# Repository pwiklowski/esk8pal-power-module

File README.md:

# esk8pal power module

This repository contains eagle project for power board that is used in esp8pal project. It contains DC-DC converter, current and voltage sensor connected do ADC chip. Board used i2c interface to connect with main board. 

 For other repositories from esk8pal project go to:

- Frontend Angular Appplication - https://github.com/pwiklowski/esk8pal-web-be
- Backend service - https://github.com/pwiklowski/esk8pal-web-be
- ESP32 Firmware - https://github.com/pwiklowski/esk8pal-device
- PWA companion application that uses Web Bluetooth API (WIP)- https://github.com/pwiklowski/esk8pal-pwa
- Android application - https://github.com/pwiklowski/esk8pal-android

## Schematic

## PCB

## Prototype

## New PCB's - power module 0.2.0 and main board 0.1.

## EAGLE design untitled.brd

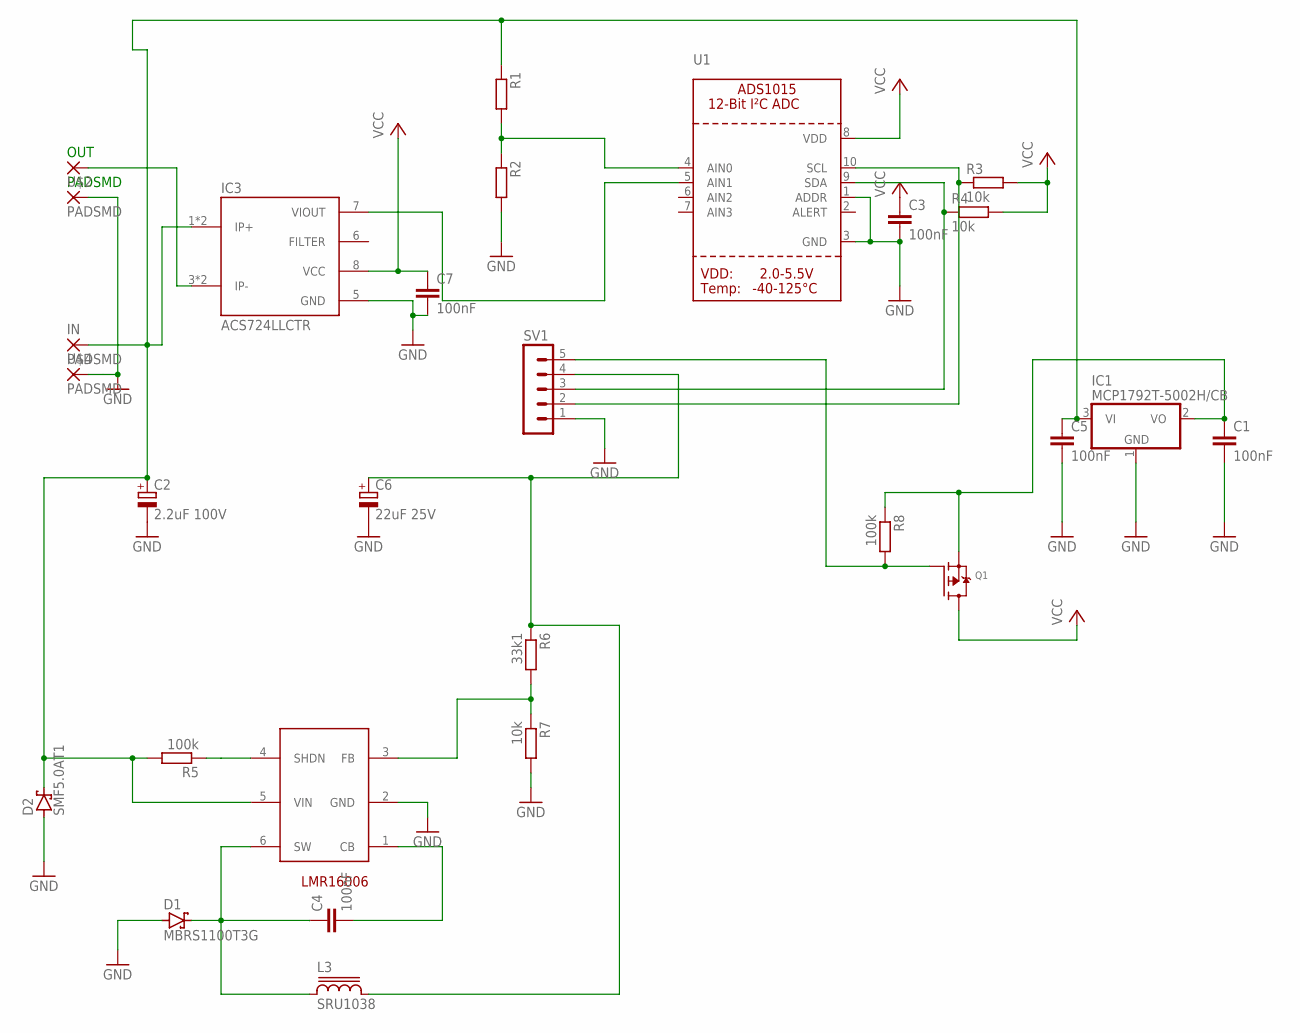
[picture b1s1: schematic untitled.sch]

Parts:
C1, C3, C4, C5, C7: 100nF; C0805
C2: 2.2uF 100V; B/3528-21R
C6: 22uF 25V; R/2012-12R
D1: MBRS1100T3G; SOD323_ST
D2: SMF5.0AT1; SOD123FL
IC1: MCP1792T-5002H/CB; SOT23
IC3: ACS724LLCTR; SO08
IN: PADSMD; PADS
L3: SRU1038
OUT: PADSMD; PADS
Q1: MOSFET-PWIDE; SOT23-WIDE
R1, R2: R-EU_R0805; R0805
R3, R4: 10k; R0805
R5: 100k; M0805
R6: 33k1; M0805
R7: 10k; M0805
R8: 100k; R0805
SV1: MA05-1
U1: ADC_ADS1015; MSOP10
U$2, U$4: PADSMD; PADS
U$5: LMR16006; TSOT23-6_DDC

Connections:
GND: C1.2, C2.-, C3.2, C5.2, C6.-, C7.2, D1.A, D2.A, IC1.1 (GND), IC3.5 (GND), R2.2, R7.2, SV1.1, U1.1 (ADDR), U1.3 (GND), U$2.P$1, U$4.P$1, U$5.2 (GND)
unnamed: IC3.7 (VIOUT), U1.5 (AIN1)
unnamed: IC3.3 (IP-), IC3.4 (IP-), OUT.P$1
unnamed: R5.1, U$5.4 (SHDN)
unnamed: C2.+, C5.1, D2.C, IC1.3 (VI), IC3.1 (IP+), IC3.2 (IP+), IN.P$1, R1.1, R5.2, U$5.5 (VIN)
unnamed: R4.1, SV1.3, U1.9 (SDA)
unnamed: R3.1, SV1.2, U1.10 (SCL)
unnamed: Q1.1 (G), R8.2, SV1.5
unnamed: C6.+, L3.2, R6.1, SV1.4
unnamed: C4.1, D1.C, L3.1, U$5.6 (SW)
unnamed: C4.2, U$5.1 (CB)
unnamed: R6.2, R7.1, U$5.3 (FB)
unnamed: C1.1, IC1.2 (VO), Q1.2 (S), R8.1
unnamed: R1.2, R2.1, U1.4 (AIN0)
VCC: C3.1, C7.1, IC3.8 (VCC), Q1.3 (D), R3.2, R4.2, U1.8 (VDD)

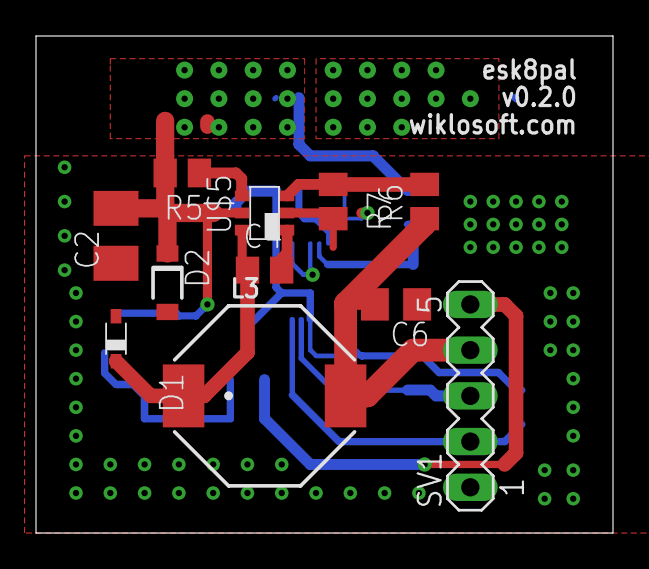
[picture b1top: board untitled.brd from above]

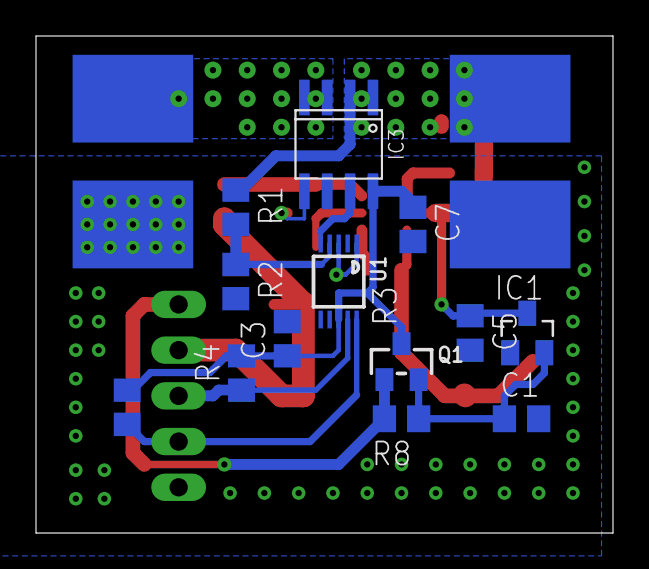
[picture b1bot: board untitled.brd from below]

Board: 2 copper layers, 32.1 x 27.6 mm, 28 parts (17 on the bottom side), 15 nets.

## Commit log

2020-05-03 Add version 1.0
2020-05-07 Add new schematic for new dc dc converter
2020-05-07 Update board layout
2020-05-09 add calculations for dcdc converter
2020-05-09 Update components
2020-05-10 Update capacitors
2020-05-10 Replace inductor with smaller one 10x10
2020-05-10 Add board layout
2020-05-12 Update board layout based on bought components
2020-05-13 Another PCB updated to match new components
2020-05-14 Add TVS to power module
2020-06-02 Update scheamictic to include dedicated ldo for senors and p mosfeto control power for sensors
2020-06-02 Update board layout for new components
2020-06-03 Update layout
2021-03-23 Use smaller current sensor and update schematic
2021-03-23 Add readme

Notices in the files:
parts and their libraries:
microbuilder: This work is placed in the public domain, and may be freely used for commercial and non-commercial work with the following conditions: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
inductor-bourns: Copyright (C) 2008, Bob Starr
